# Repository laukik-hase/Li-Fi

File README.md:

# Li-Fi

Repository for a R&D project based on the principles of Li-FI for communication and sharing of data between multiple devices using visible light at SRA, VJTI

## Note: 

All the material posted here (datasheets, books and research papers) are properties of the respective authors, is solely for sharing and informative purposes.

## Flow:

## Tasks accomplished:
1. Transfer of text (.txt), image (.png/.jpeg) and .pdf files from one laptop to another, using the prototype as shown, which uses the basic 3V, 20mA LED and simple IR photodiode 
(Range: 5 cm; Speed: 3600 baud)

2. Successful testing of the BPW21R photodiode, for faster response and better range
 (Range: 35 cm; Speed: 19200 baud)
 
3. Designing of analog filters for reducing the effect of ambient light and AC noise and increasing the range of communication (to be implemented)

4. Designing a simple protocol using UART as a framework for efficient and error-free transmission (to be tested)

## Future goals:
1. Implementation of a Master LED (240V, 50 Hz AC) for the transmission side

2. Implementation of the analog filters (namely, High-Pass and Notch) for noise-reduction

3. Creating a robust protocol for the error-free data transmission and receiving; exploring the scope of socket programming and TCP/IP for LiFi

4. Maximizing the speed of communication by implementing faster Op-Amps, LEDs and PDs and replacing the CP2102 module with a faster and reliable alternative

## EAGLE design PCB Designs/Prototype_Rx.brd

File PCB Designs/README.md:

# PCB Designs:

## Transmitter:

Components: MOSFET n-channel - IRF540N & 12V OSRAM SMD LEDs

## Receiver:

Components: Photodiode - BPW34 & Op-Amp - LM324 (LM7171)

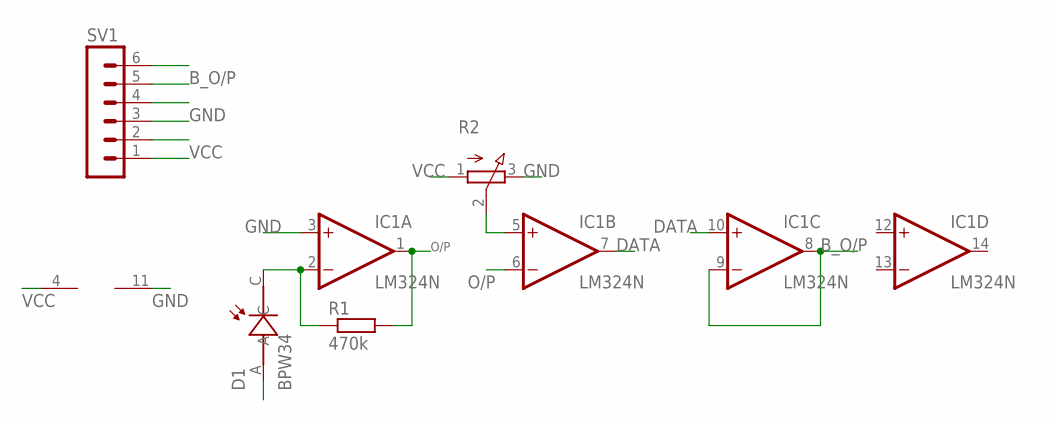
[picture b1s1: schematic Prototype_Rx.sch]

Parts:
D1: BPW34; PHODET_BPW34
IC1: LM324N; DIL14
R1: 470k; 0207/10
R2: 3RP/1610N
SV1: MA06-1

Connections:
B_O/P: IC1.8 (OUT), IC1.9 (-IN), SV1.5, SV1.6
DATA: IC1.7 (OUT), IC1.10 (+IN)
GND: D1.A, IC1.3 (+IN), IC1.11 (V-), R2.3 (E), SV1.3, SV1.4
unnamed: D1.C, IC1.2 (-IN), R1.1
unnamed: IC1.5 (+IN), R2.2 (S)
O/P: IC1.1 (OUT), IC1.6 (-IN), R1.2
VCC: IC1.4 (V+), R2.1 (A), SV1.1, SV1.2

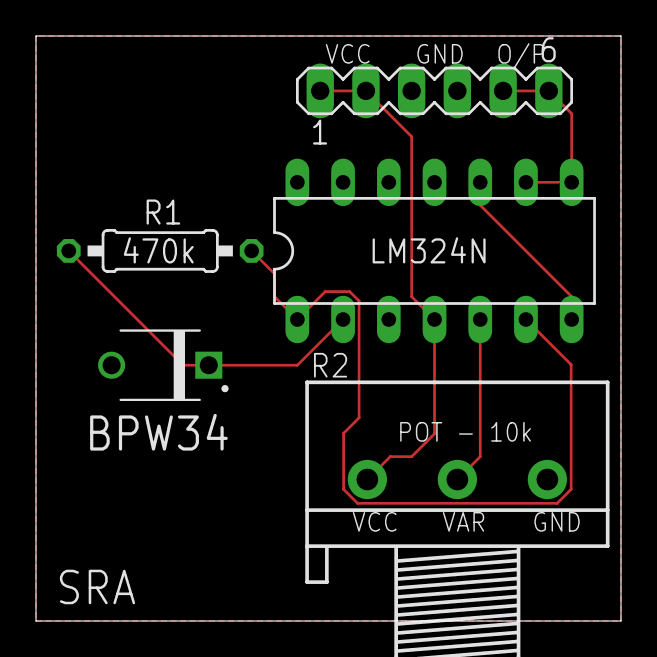
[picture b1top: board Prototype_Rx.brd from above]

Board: 2 copper layers, 32.5 x 32.5 mm, 5 parts (0 on the bottom side), 7 nets.

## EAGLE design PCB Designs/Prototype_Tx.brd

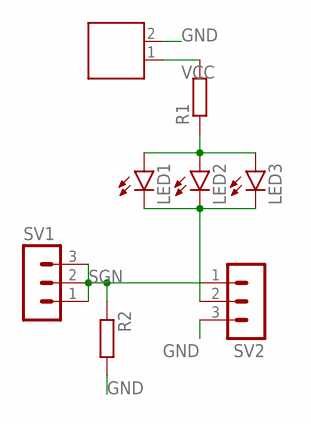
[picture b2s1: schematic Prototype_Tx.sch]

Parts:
12V: 691131710002
LED1, LED2, LED3: LEDCHIP-LED0805; CHIP-LED0805
R1: R-EU_0207/10; 0207/10
R2: R-EU_0204/7; 0204/7
SV1, SV2: MA03-1

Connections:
GND: 12V.2, R2.2, SV2.3
unnamed: LED1.A, LED2.A, LED3.A, R1.1
unnamed: LED1.C, LED2.C, LED3.C, SV2.2
SGN: R2.1, SV1.1, SV1.2, SV1.3, SV2.1
VCC: 12V.1, R1.2

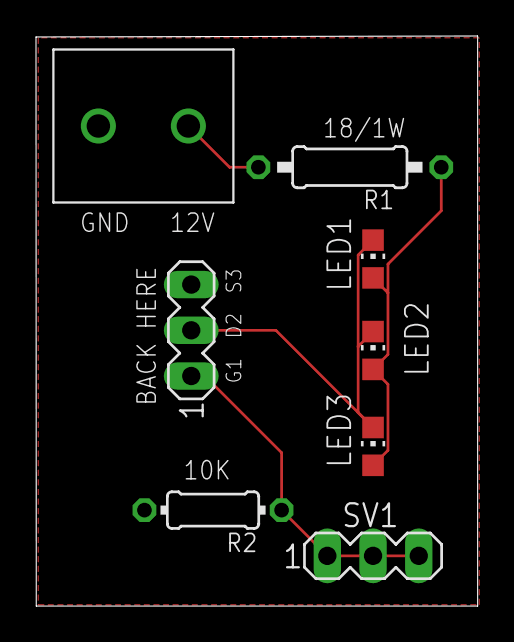
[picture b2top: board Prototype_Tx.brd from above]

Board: 2 copper layers, 24.5 x 31.7 mm, 8 parts (0 on the bottom side), 5 nets.

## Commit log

2019-09-23 Update Designs
2019-11-13 final ckt added
2019-11-13 tx added
2019-11-13 Code Reload
2019-11-14 contributer
2019-11-14 gui with load and save popup
2019-11-15 final hardware images
2019-11-15 report upload
2020-04-02 updated protocol based transfer on arduino
2020-04-08 Create LICENSE

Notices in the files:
parts and their libraries:
Wurth_Elektronik_Electromechanic_Termina: Copyright: Würth Elektronik
